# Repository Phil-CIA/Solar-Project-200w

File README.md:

# Solar Project 200W

Solar Project 200W is a prototype-first hardware and firmware effort for a 200W-class solar charging system built around a 4S LiFePO4 battery domain.

## What this repository is for

- Designing and validating a safe MPPT charger path
- Defining control, telemetry, and protection behavior
- Tracking design decisions, handoffs, and bring-up evidence

## Rev2 preparation

Phil selected **retain LM51772 for Rev2**. Open `hardware\kicad\solar-project\Solar Project Rev2.kicad_pro` for new Rev2 work; its schematic/PCB are a metadata-only copy of the reconciled Rev1 development source at `32243b5` (tag `rev2-development-baseline-2026-11-09`), not an implemented or qualified redesign and not for fabrication. See the [revision index](hardware/kicad/solar-project/REVISION-INDEX.md), [consolidation/change register](docs/rev-two-consolidation.md), and current [handoff](HANDOFF.md) for source identity, bench evidence and unresolved work. The controller-comparison requirement in [#20](https://github.com/Phil-CIA/Solar-Project-200w/issues/20) remains open; no BQ25756 evaluation or purchase is requested.

## Rev 1 manufactured baseline

- Only Rev 0 and Rev 1 have been manufactured; Rev 2 is a copied development starting set. Rev 1 is the current production revision. The production release at `C:\Users\user\OneDrive\JLCPCB files\Solar Charger\Rev 1` is authoritative for board identity, manufacturing and board-specific tests. Repository copies support continued development; the schematic, project and BOM differences are described in the board notes.
- Rev 1 is assembled; the supplied manufacturing package and both-side photos are recorded in [board notes](docs/rev-one-board-notes.md).
- Retain the Rev 1 [development tracker](https://github.com/Phil-CIA/Solar-Project-200w/issues/1) and [working plan](docs/rev-one-closure-plan-2026-09-16.md#6-assembled-board-execution-and-issue-1-closure) as qualification references. Later bench findings and current next steps are linked from the handoff; old unpowered checkpoints are not the current board state.
- This is a hobby prototype: keep useful notes and relevant checks, not a formal lab dossier. Assembly does not establish working charging or full-power performance.
- Rev 1 STM32G473 bring-up firmware through `ff89791` is already on `main`; see [firmware notes](firmware/README.md). That is development progress, not proof of board compatibility or a passing powered test.

## System baseline

- PV class: 2x100W panels in parallel (DEC-051)
- Battery class: 12.8V LiFePO4 (4S)
- Rev 1 design targets: 125 W continuous output, 150 W maximum PV operating power, 8-10 A nominal charging, approximately 12 A hardware protection pending verification

## Project structure

- [docs/](docs/): requirements, architecture, decisions, test plans, phase reviews
- [hardware/](hardware/): KiCad files, MPPT notes, wiring maps, implementation checklists
- [firmware/](firmware/): firmware workspace and bring-up software notes

## Start here

1. [HANDOFF.md](HANDOFF.md) - current checkpoint and next step
2. [docs/rev-one-board-notes.md](docs/rev-one-board-notes.md) - working board baseline and known differences
3. [docs/README.md](docs/README.md) - engineering references
4. [docs/decisions-log.md](docs/decisions-log.md) - retained design decisions
5. [SOLAR_HANDOFF_2026-09-19.md](SOLAR_HANDOFF_2026-09-19.md) and [SOLAR_HANDOFF_2026-09-18.md](SOLAR_HANDOFF_2026-09-18.md) for the historical Rev 1 fabrication closeout
6. [hardware/kicad/solar-project/REVISION-INDEX.md](hardware/kicad/solar-project/REVISION-INDEX.md) for KiCad source-of-truth rules

## Simulation workflow

The PV switch gate-drive concept should be verified with SPICE as part of the normal review loop. The project-local LTspice assets are in [hardware/kicad/solar-project/spice](hardware/kicad/solar-project/spice), including the schematic draft [hardware/kicad/solar-project/spice/pv_switch_gate_drive.asc](hardware/kicad/solar-project/spice/pv_switch_gate_drive.asc) and the launcher [hardware/kicad/solar-project/spice/run_ltspice_pv_gate_drive.cmd](hardware/kicad/solar-project/spice/run_ltspice_pv_gate_drive.cmd).

A provisional LTspice integration harness is also present at [hardware/kicad/solar-project/spice/90_system_integration_harness_ltspice.cir](hardware/kicad/solar-project/spice/90_system_integration_harness_ltspice.cir). It is a simplified, staged model of the PV input, buck power stage, and battery boundary. The current run converged to about 13.64 V at the output node and 13.98 V at the battery bus at 4 ms, which is consistent with a basic charging path but still not hardware-validated.

Earlier simulation identified a gate-drive margin problem in the arrangement it modeled. That historical result is not a measured failure of the assembled Rev 1 U14/Q5/Q6 protection circuit; confirm the topology against the Rev 1 production release and use matching low-energy checks before drawing that conclusion.

## Safety notice

This project includes high-current DC power electronics and planned AC-domain integration.
Use staged, current-limited bring-up and treat all safety checks as mandatory gates.

## Session continuity

- [HANDOFF.md](HANDOFF.md)
- [NEXT_CHAT_PROMPT.md](NEXT_CHAT_PROMPT.md)

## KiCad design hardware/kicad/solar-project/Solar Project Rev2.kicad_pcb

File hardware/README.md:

# Hardware

Store hardware development assets here.

Suggested structure:
- `schematics/`
- `pcb/`
- `bom/`
- `manufacturing/`
- `validation/`

Add tool/version notes and board revision history as the project evolves.

## Phase 1 Kickoff Artifacts

- `mppt/block-diagram.md`
- `mppt/schematic-exploration-checklist.md`
- `mppt/interface-assumptions.md`
- `mppt/schematic-notes.md`
- `mppt/net-plan.md`
- `mppt/component-shortlist-template.md`
- `mppt/kicad-implementation-checklist.md`
- `mppt/envelope-decision-worksheet.md`
- `mppt/decision-update-template.md`
- `mppt/buck-topology-notes.md`
- `mppt/github-reference-notes.md`
- `mppt/buck-symbol-placement-checklist.md`
- `mppt/pv-input-stage.md`
- `mppt/pv-input-wiring-map.md`
- `mppt/buck-power-stage-wiring-map.md`
- `mppt/sheet2-component-picks.md`

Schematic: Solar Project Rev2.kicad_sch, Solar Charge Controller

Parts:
10mm1, 10mm2: 10mm LOGO
C1, C8, C12, C22, C28, C33, C44, C45, C46, C47, C48, C51, C54, C57, C58, C59, C60, C64: 100nF; C_0805; Voltage Rated 100V; Tolerance ±10%; Part CL21B104KCFNNNE; LCSC C28233
C2, C55, C56: 1uF; C_0805; Voltage Rated 50V; Tolerance ±10%; Part CL21B105KBFNNNE; LCSC C28323
C3: 100uF; CP_Radial_D6.3mm_P2.50mm; LCSC C49232871
C7: 2.2uF; C_1206; Voltage Rated 100V; Tolerance ±10%; Part CC1206KKX7R0BB225; LCSC C577211
C9, C13: 2.2nF; C_0805; Voltage Rated 50V; Tolerance ±5%; Part CL21C222JBFNNNE; LCSC C28260
C10: 47pF; C_0805; Voltage Rated 50V; Tolerance ±5%; Part CL21C470JBANNNC; LCSC C14857
C14, C53: 100uF; C_1206; Voltage Rated 6.3V; Tolerance ±20%; Part CL31A107MQHNNNE; JLCPCB ID C45783
C15, C34, C35: 2.2uF; C_1206; Voltage Rated 50V; Tolerance ±10%; Part CL31B225KBHNNNE; LCSC C50254
C18: 560uF; CP_Elec_10x12.6; LCSC C264031
C19, C21, C30, C31: 47uF; CP_Radial_D8.0mm_P3.50mm; LCSC C44606514
C20: 180pF; C_0805; LCSC C1794
C23: 100nF; C_0805; LCSC C28233
C24: 22nF; C_0805; LCSC C1710
C25: 1.5nF; C_0805; LCSC C1590
C26: 33nF; C_0805; LCSC C1738
C27, C29: 22uF; C_0805; Voltage Rated 25V; Tolerance ±20%; Part CL21A226MAQNNNE; LCSC C45783
C49, C50: 33pF; C_0805; Voltage Rated 50V; Tolerance ±5%; Part CC0805JRNPO9BN330; LCSC C1798
C52: 220nF; C_0805; Voltage Rated 50V; Tolerance ±10%; Part CL21B224KBFNNNE; LCSC C5378
C61: DNP; C_0805; Voltage Rated 100V; Tolerance ±10%; Part CL21B104KCFNNNE; not fitted
C62, C63: 100nF; C_0805_2012Metric; Voltage Rated 100V; Tolerance ±10%; Part CL21B104KCFNNNE; LCSC C28233
D1, D5: 1SMA4742A; D_DO-214AC(SMA); Part 1SMA4742A; LCSC C19077480
D2: SMBJ48CA; D_SMB; Part SMBJ48CA; LCSC C151264
D3: USBLC6-2SC6; SOT-23-6; MPN USBLC6-2SC6; Digi-Key_PN 497-5235-1-ND
D6, D7, D10: 1N5819WS; D_SOD-323; Forward Voltage (Vf@If) 600mV@1A; Reverse Voltage (Vr) 40V; Part 1N5819WS; LCSC C191023
D8, D11: WS2812B; LED-SMD_4P-L1.6-W1.5_XL-1615RGBC-WS2812B; LCSC C5349954
D9: Green; D_0805; Forward Voltage (VF) 1.6V~2.6V; Part KT-0805G; LCSC C2297
D12: Yellow; D_0805; Forward Voltage (VF) 1.6V~2.6V; Part KT-0805Y; LCSC C2296
F1, F2: 3522-2; Automotive fuse holder keystone 3522-2_KEY; Part - USA Keystone 3522-2, sourced via Digikey/Mo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; LCSC C3204137
J1, J3: Screw_Terminal_01x02; TerminalBlock_Phoenix_MKDS-1,5-2-5.08_1x02_P5.08mm_Horizont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; LCSC C8439
J2: USB4105-GF-A; GCT_USB4105-GF-A; PARTREV B4; LCSC C3020560
J7: Fan; PinHeader_1x03_P2.54mm_Vertical; LCSC C29275
J8: I2C bus; PinHeader_1x04_P2.54mm_Vertical
J9: FTSH-105-01-L-DV-007-K; MPN FTSH-105-01-L-DV-007-K; LCSC C5160761
JP1: SolderJumper_2_Bridged; SolderJumper-2_P1.3mm_Bridged_Pad1.0x1.5mm
JP2: SolderJumper_2_Open; SolderJumper-2_P1.3mm_Open_RoundedPad1.0x1.5mm
L2: L; L_APV_APH1240; LCSC C49308530
L3: L; L_KOHERelec_MDA7030; LCSC C49333024
M1, M2, M3, M4: CSD18540Q5B; TDSON-8-1; LCSC C86513
NT1, NT2, NT3, NT4, NT5, NT6, NT7, NT8: NetTie_2; NetTie-2_SMD_Pad0.5mm
Q2, Q3, Q7: 2N7002K; Q_SOT-23; Part 2N7002K; LCSC C22379475
Q4: HSBA0119; PQFN-8-EP_6x5mm_P1.27mm_Generic; LCSC C53244070
Q5, Q6: BSC040N10NS5; TDSON-8-1; LCSC C534334
R1, R2, R32, R38, R67: 100kΩ; R_0805; Overload Voltage (Max) 150V; Tolerance ±1%; Part 0805W8F1003T5E; LCSC C17416
R3: 76.8k; R_0805; LCSC C3000581; not fitted
R4, R26, R27, R41, R65, R69, R70, R71, R72, R73: 10Ω; R_0805; Overload Voltage (Max) 150V; Tolerance ±1%; Part 0805W8F100JT5E; LCSC C17414
R5, R44, R45: 4.7kΩ; R_0805; Overload Voltage (Max) 150V; Tolerance ±1%; Part 0805W8F4701T5E; LCSC C17673
R6, R19, R34, R36, R47, R48, R52, R53, R54, R55, R56, R57, R58, R59, R82, R86, R91, R92, R93, R94, R95, R96, R97, R98, R100: 10kΩ; R_0805; Overload Voltage (Max) 150V; Tolerance ±1%; Part 0805W8F1002T5E; LCSC C17414
R7, R10, R61: 20kΩ; R_0805; Overload Voltage (Max) 150V; Tolerance ±1%; Part 0805W8F2002T5E; LCSC C17523
R8: 27kΩ; R_0805; Overload Voltage (Max) 150V; Tolerance ±1%; Part 0805W8F2702T5E; LCSC C17547
R9: 180k; R_0805; LCSC C17497
R11, R39: 330Ω; R_0805; Overload Voltage (Max) 150V; Tolerance ±1%; Part 0805W8F3300T5E; LCSC C17650
R12: 6.8kΩ; R_0805; Overload Voltage (Max) 150V; Tolerance ±1%; Part 0805W8F6801T5E; LCSC C17730
R13: 1MΩ; R_0805; Overload Voltage (Max) 150V; Tolerance ±1%; Part 0805W8F1004T5E; LCSC C17514
R14: 330kΩ; R_0805; Overload Voltage (Max) 150V; Tolerance ±1%; Part 0805W8F3303T5E; LCSC C17651
R15: 2kΩ; R_0805; Overload Voltage (Max) 150V; Tolerance ±1%; Part 0805W8F2001T5E; LCSC C17537
R16, R22, R75, R80: 5mΩ; RES_2012_SUS- wide 0805; Tolerance ±1%; Part KRL2012E-M-R005-F-T5; LCSC C2073455
R17: 5.62k; R_0805; LCSC C2933470
R18: 76.8k; R_0805; LCSC C3000581
R20: 499k; R_0805; LCSC C119857
R21: 102k; R_0805; LCSC C119830
R23: 75kΩ; R_0805; Overload Voltage (Max) 150V; Tolerance ±1%; Part 0805W8F7502T5E; LCSC C17743
R24, R62: 5.1kΩ; R_0805; Overload Voltage (Max) 150V; Tolerance ±1%; Part 0805W8F5101T5E; LCSC C17700
R25: 5.62k; R_0805; LCSC C2933470; not fitted
R28: 51.7k; R_0805; LCSC C119851
R29: 20.5k; R_0805; LCSC C119842
R30: 40.2k; R_0805; LCSC C119848
R31: 2.43k; R_0805; LCSC C119853
R33, R49, R63, R64: 0Ω; R_0805; Overload Voltage (Max) 150V; Tolerance ±1%; Part 0805W8F0000T5E; LCSC C17888
R35, R81: 180kΩ; R_0805; Overload Voltage (Max) 150V; Tolerance ±1%; Part 0805W8F1803T5E; LCSC C17497
R37, R66: 2.2MΩ; R_0805; Overload Voltage (Max) 150V; Tolerance ±1%; Part 0805W8F2204T5E; LCSC C17539
R40, R43, R74: 100kΩ; R_0805; Overload Voltage (Max) 150V; Tolerance ±1%; Part Number RC0603FR-07100KL; JLCPCB ID C25803
R42, R83, R84, R85: 1kΩ; R_0805; Overload Voltage (Max) 150V; Tolerance ±1%; Part 0805W8F1001T5E; LCSC C17513
R46: 32.4kΩ; R_0805; Overload Voltage (Max) 150V; Tolerance ±1%; Part RC0805FR-0732K4L; LCSC C2930193
R50: 10kΩ; R_0805; Overload Voltage (Max) 150V; Tolerance ±1%; Part 0805W8F1002T5E; LCSC C17415; not fitted
R51: 12kΩ; R_0805; Overload Voltage (Max) 150V; Tolerance ±1%; Part 0805W8F1202T5E; LCSC C17444
R60: 1.5kΩ; R_0805; Overload Voltage (Max) 150V; Tolerance ±1%; Part 0805W8F1501T5E; LCSC C17515
R68: 1.3k; R_0805; LCSC C2933303
R76, R77: KRL2012E-M-R005-F-T5; RES_2012_SUS- wide 0805; Tolerance ±1%; Part KRL2012E-C-R010-F-T5; LCSC C2073455
R78, R79: .001; R_2512_6332Metric; Tolerance ±1%; Part DSLR-M-3-1F; LCSC C41382682
R87, R88, R89, R90: 100Ω; R_0805; Overload Voltage (Max) 150V; Tolerance ±1%; Part 0805W8F1000T5E; LCSC C17408
R99: 56kΩ; R_0805; Overload Voltage (Max) 150V; Tolerance ±1%; Part 0805W8F5602T5E; LCSC C17756
R101: 33kΩ; R_0805; Overload Voltage (Max) 150V; Tolerance ±1%; Part 0805W8F3302T5E; LCSC C17633
S1: Tactile Button, 160gf; SW_TS-1088-AR02016; Voltage Rating (Dc) 12V; Part TS-1088-AR02016; LCSC C720477
SW1, SW2, SW3, SW4, SW5: Tactile Button, 160gf; SW-SMD_4P-L5.1-W5.1-P3.70-LS6.5-TL-2; Voltage Rating (Dc) 12V; Part TS-1187A-B-A-B; LCSC C318884
TP1: TestPoint_Small; PinHeader_1x01_P2.54mm_Vertical; not fitted
TP15, TP16, TP17, TP18: 5015; TestPoint_Keystone_5015_Micro_Mini; PARTREV F; LCSC C5199798
U1: STM32G473CEU6; QFN-48-1EP_7x7mm_P0.5mm_EP5.6x5.6mm; LCSC C1342773
U2: ESP32-C3 SuperMini (16-pin); ESP32 C3 mini
U3: CP2102-GMR; WQFN-28_L5.0-W5.0-P0.50-BL-EP3.2; Supply Voltage 3V~3.6V; Part CP2102-GMR; LCSC C6568
U4: LM5163; Texas_R-PDSO-G8_EP2.95x4.9mm_Mask2.4x3.1mm_ThermalVias; LCSC C2873264
U5: LP5912-3.3DRV; WSON-6-1EP_2x2mm_P0.65mm_EP1x1.6mm_ThermalVias; LCSC C114569
U6: LM51772QRHARQ1; VFQFN-40-1EP_6x6mm; LCSC C41383743
U7: AHT20; Humidity sensor; PARTREV V1.0; LCSC C2757850
U8: SSD1306_OLED; 0.96 inOLED display SSD1306; LCSC C5248080
U9: LMV393; SOIC-8-1EP_3.9x4.9mm_P1.27mm_EP2.29x3mm_ThermalVias; LCSC C7984
U10, U11, U12: INA241A3IDDFR; TSOT-23-8; Part INA241A3IDDFR; LCSC C129346
U14: LM74502HDDFR; Texas_DDF0008A_SOT-8_1.6x2.9mm_P0.65mm; LCSC C5219202
U15: TXU0204PWR; TSSOP-14_4.4x5mm_P0.65mm; LCSC C4363888
X2: X49SM8MSD2SC; CRYSTAL-SMD_L11.5-W4.8-LS12.7; Frequency Tolerance ±20ppm; Part X49SM8MSD2SC; LCSC C12674

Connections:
BATT_PACK_POS: J3.2, NT8.1, R78.1, R79.1, R99.1
BTN_DN_N: SW2.1 (A), U1.33 (PA11)
BTN_ENT_N: SW5.1 (A), U1.47 (PB9)
BTN_LT_N: SW4.1 (A), U1.34 (PA12)
BTN_RT_N: SW3.1 (A), U1.39 (PC10)
BTN_UP_N: SW1.1 (A), U1.38 (PA15)
CHG_OUT_POS: D6.2, F2.3, F2.4, J7.3, Q6.5 (D), R20.1, R81.1, U6.18 (VOUT)
CTRL_3V3: C12.1, C44.1, C48.1, C53.1, C54.1, C55.1, C63.1, J8.3, J9.1 (VTref), R5.2, R19.1, R21.1, R34.1, R39.1, R44.1, R45.1, R51.1, R53.1, R54.1, R55.1, R56.1, R57.1, R58.1, R59.1, R74.1, R91.1, R92.1, R97.1, R98.1, TP17.1, U1.1 (VBAT), U1.20 (VREF+), U1.21 (VDDA), U1.23 (VDD), U1.35 (VDD), U1.48 (VDD), U3.6 (VDD), U5.1 (OUT), U6.38 (RST), U7.2 (VDD), U8.2 (VCC), U9.8 (V+), U11.7 (REF1), U15.1 (VCCA), U15.8 (OE)
CTRL_5V: C9.1, C14.1, C51.2, C56.1, C57.1, D7.1, D8.2 (VDD), D10.1, D11.2 (VDD), L3.2, R10.2, R11.1, TP18.1, U2.16 (5V), U5.4 (EN), U5.6 (IN), U10.6 (V+), U11.6 (V+), U12.6 (V+)
CTRL_EN_CHG: R73.1, U1.25 (PB12)
CTRL_SUPPLY_IN: C15.1, D6.1, R13.1, U4.2 (VIN)
CTS: U1.14 (PA6), U3.23 (CTS)
ESP_3V3_U2: C62.1, R93.1, R94.1, R95.1, R96.1, U2.14 (3.3V), U15.14 (VCCB)
ESP_CONSOLE_RX: R88.2, R96.2, U2.7 (GPIO20)
ESP_CONSOLE_RX_STM: R92.2, U1.22 (PB10), U15.3 (A2)
ESP_CONSOLE_TX: R94.2, U2.8 (GPIO21), U15.10 (B4)
ESP_CONSOLE_TX_STM: R90.1, R98.2, U1.24 (PB11)
ESP_DATA_RX: R87.2, R95.2, U2.9 (GPIO0)
ESP_DATA_RX_STM: R91.2, U1.41 (PB3), U15.2 (A1)
ESP_DATA_TX: R93.2, U2.10 (GPIO1), U15.11 (B3)
ESP_DATA_TX_STM: R89.1, R97.2, U1.42 (PB4)
FAN_TACH: J7.2, U1.43 (PB5)
FAULT_OCP: R53.2, U1.17 (PB0), U9.7
FAULT_OVP: R19.2, U1.18 (PB1), U9.1
Fan Control: R4.1, U1.40 (PC11)
HO1: M1.4 (G), R69.1
HO2: M4.4 (G), R71.1
I2C CLK: J8.1, R44.2, U1.45 (PB7), U6.6 (SCL_CFG4), U7.3 (SCL), U8.3 (SLC)
I2C DATA: J8.4, R45.2, U1.44 (PB6), U6.5 (SDA_CFG3), U7.4 (SDA), U8.4 (SDA)
I_BATT_+: NT7.1, U11.8 (+)
I_BATT_-: NT8.2, U11.1 (-)
I_in_+: NT4.1, U12.8 (+)
I_in_-: NT3.1, U12.1 (-)
LO1: M2.4 (G), R70.1
LO2: M3.4 (G), R72.1
unnamed: C9.2, C10.1, R12.2
unnamed: C24.1, R31.1
unnamed: D8.4 (DIN), U1.19 (PB2)
unnamed: D9.2, R11.2
unnamed: D8.1 (DOUT), D11.4 (DIN)
unnamed: D12.2, R39.2
unnamed: F2.1, F2.2, NT7.2, R78.2, R79.2
unnamed: F1.3, F1.4, J1.1
unnamed: J2.A5 (CC1), R24.2
unnamed: J2.B5 (CC2), R62.2
unnamed: D3.3 (I/O2), J2.A7 (DN1), J2.B7 (DN2)
unnamed: D3.1 (I/O1), J2.A6 (DP1), J2.B6 (DP2)
unnamed: J2.A8 (SBU1), J2.B8 (SBU2)
unnamed: J7.1, Q3.3 (D)
unnamed: JP1.1 (A), JP2.1 (A), U6.14 (FB_INT)
unnamed: Q2.3 (D), R42.1, R43.2
unnamed: Q2.1 (G), R40.2, R41.2
unnamed: Q3.1 (G), R1.1, R4.2
unnamed: D1.2, Q4.4 (G), R42.2
unnamed: D5.1, Q5.4 (G), Q6.4 (G), R2.2, R65.2
unnamed: Q7.1 (G), R73.2, R74.2
unnamed: R7.2, R10.1
unnamed: R9.1, R12.1
unnamed: R14.2, R15.1
unnamed: R37.2, R66.1
unnamed: R46.1, R68.1
unnamed: R60.1, R61.2
unnamed: R84.1, U12.5
unnamed: R85.1, U11.5
unnamed: R99.2, R100.1, R101.1
unnamed: R54.2, SW1.2 (B)
unnamed: R55.2, SW2.2 (B)
unnamed: R56.2, SW3.2 (B)
unnamed: R57.2, SW4.2 (B)
unnamed: R58.2, SW5.2 (B)
unnamed: R86.1, U1.46 (PB8-BOOT0)
unnamed: C50.1, U1.5 (PF0-OSC_IN), X2.1
unnamed: C49.1, U1.6 (PF1-OSC_OUT), X2.2
unnamed: D3.6 (I/O1), U3.4 (D+)
unnamed: D3.4 (I/O2), U3.5 (D-)
unnamed: R5.1, U3.9 (RST#)
unnamed: C13.2, U4.7 (BST)
unnamed: R13.2, R14.1, U4.3 (EN/UVLO)
unnamed: C10.2, R6.2, R7.1, U4.5 (FB)
unnamed: R8.1, U4.4 (RON)
unnamed: C13.1, L3.1, R9.2, U4.8 (SW)
unnamed: R33.1, U6.9 (ADDR_SLOPE_CFG1)
unnamed: R30.1, U6.10 (CDC)
unnamed: R29.1, U6.8 (CFG2)
unnamed: C24.2, C25.2, U6.13 (COMP)
unnamed: C20.1, C61.1, R26.2, U6.22 (CSA)
unnamed: C20.2, C61.2, R27.2, U6.21 (CSB)
unnamed: C22.1, U6.25 (HB1)
unnamed: C23.1, U6.31 (HB2)
unnamed: R69.2, U6.24 (HO1)
unnamed: R71.2, U6.32 (HO2)
unnamed: R68.2, U6.16 (ILIMCOMP_ISET)
unnamed: R63.1, U6.19 (ISNSN)
unnamed: R64.1, U6.20 (ISNSP)
unnamed: R70.2, U6.27 (LO1)
unnamed: R72.2, U6.30 (LO2)
unnamed: R32.2, U6.7 (MODE)
unnamed: R28.1, U6.12 (RT)
unnamed: C26.2, U6.2 (SS_ATRK)
unnamed: C27.1, C46.1, U6.1 (VCC1)
unnamed: U7.1 (NC), U7.6 (NC)
unnamed: R65.1, U14.6 (GATE)
unnamed: R66.2, R67.1, U14.7 (OV)
unnamed: C52.2, U14.4 (VCAP)
unnamed: R89.2, U15.4 (A3Y)
unnamed: R90.2, U15.5 (A4Y)
unnamed: R87.1, U15.13 (B1Y)
unnamed: R88.1, U15.12 (B2Y)
OCP_MEAS: R49.1, R83.1, U10.5
OCP_REF: R51.2, R52.1, U9.6 (-)
OCP_SENSE: R49.2, R50.1, U9.5 (+)
OVP_REF: R21.2, R48.1, U9.2 (-)
OVP_SENSE: R20.2, R47.1, U9.3 (+)
PA0: C58.1, R83.2, U1.8 (PA0)
PA1: C59.1, R84.2, U1.9 (PA1)
PC4: C60.1, R85.2, U1.16 (PC4)
PV_FUSED_POS: D2.2, F1.1, F1.2, NT4.2, R35.1, R76.1, R77.1
PV_IN_POS: C7.1, C8.1, C19.1, C21.1, C28.1, C30.1, C31.1, M1.5 (D), Q4.5 (D), R18.1, R23.1, TP16.1, U6.36 (VIN), U6.40 (BIAS)
PV_Q4_SOURCE: D1.1, NT3.2, Q4.1 (S), Q4.2 (S), Q4.3 (S), R43.1, R76.2, R77.2
PWR_NEG: C1.2, C2.2, C3.2, C7.2, C8.2, C12.2, C14.2, C15.2, C18.2, C19.2, C21.2, C25.1, C26.1, C27.2, C28.2, C29.2, C30.2, C31.2, C33.1, C34.2, C35.2, C44.2, C45.2, C46.2, C47.2, C48.2, C49.2, C50.2, C51.1, C53.2, C54.2, C55.2, C56.2, C57.2, C58.2, C59.2, C60.2, C62.2, C63.2, C64.2, D2.1, D3.2 (GND), D8.3 (GND), D9.1, D11.3 (GND), D12.1, J1.2, J2.A1_B12 (GND), J2.B1_A12 (GND__1), J2.SH1 (SHELL_GND), J2.SH2 (SHELL_GND__1), J2.SH3 (SHELL_GND__2), J2.SH4 (SHELL_GND__3), J3.1, J8.2, J9.3 (GND), J9.5 (GND), J9.9 (GNDDetect), M2.1 (S), M2.2 (S), M2.3 (S), M3.1 (S), M3.2 (S), M3.3 (S), Q2.2 (S), Q3.2 (S), Q7.2 (S), R1.2, R6.1, R8.2, R15.2, R17.2, R24.1, R25.2, R28.2, R29.2, R30.2, R31.2, R33.2, R36.2, R38.2, R40.1, R46.2, R47.2, R48.2, R50.2, R52.2, R60.2, R62.1, R67.2, R82.2, R86.2, R100.2, S1.2 (B), SW1.3 (C), SW1.4 (D), SW2.3 (C), SW2.4 (D), SW3.3 (C), SW3.4 (D), SW4.3 (C), SW4.4 (D), SW5.3 (C), SW5.4 (D), TP15.1, U1.49 (VSS), U2.15 (GND), U3.3 (GND), U4.1 (GND), U4.9 (TH_pd), U5.5 (GND), U5.7 (EP), U6.3 (SYNC), U6.4 (DTRK), U6.17 (AGND), U6.28 (PGND), U6.41 (GND), U7.5 (GND), U8.1 (GND), U8.5 (GND), U8.6 (GND), U8.7 (GND), U8.8 (GND), U9.4 (V-), U9.9 (EP), U10.2 (GND), U10.3 (REF2), U10.4 (GND), U10.7 (REF1), U11.2 (GND), U11.3 (REF2), U11.4 (GND), U12.2 (GND), U12.3 (REF2), U12.4 (GND), U12.7 (REF1), U14.2 (GND), U15.7 (GND)
RTS: U1.15 (PA7), U3.24 (RTS)
RXD: U1.31 (PA9), U3.25 (RXD)
SRC: D5.2, Q5.1 (S), Q5.2 (S), Q5.3 (S), Q6.1 (S), Q6.2 (S), Q6.3 (S), R2.1, U14.8 (SRC)
STM_NRST: C47.1, J9.10 (~RESET), R59.2, S1.1 (A), U1.7 (PG10-~RST)
SWCLK: J9.4 (SWCLK/TCK), U1.37 (PA14)
SWDIO: J9.2 (SWDIO/TMS), U1.36 (PA13)
SW_1: C22.2, M1.1 (S), M1.2 (S), M1.3 (S), M2.5 (D), NT2.2, R22.1, R75.1, U6.23 (SW1)
SW_1_+: NT2.1, R26.1
SW_1_-: L2.1, NT1.1, NT1.2, R22.2, R27.1, R75.2
SW_2: C23.2, L2.2, M3.5 (D), M4.1 (S), M4.2 (S), M4.3 (S), U6.33 (SW2)
TXD: U1.32 (PA10), U3.26 (TXD)
U6_FLT: R34.2, U1.2 (PC13), U6.11 (FLT)
U6_VCC2: C29.1, C45.1, JP1.2 (B), R32.1, U6.29 (VCC2)
VBUS: C1.1, C2.1, D3.5 (VBUS), D7.2, D10.2, J2.A4_B9 (VBUS), J2.B4_A9 (VBUS__1), U3.7 (REGIN), U3.8 (VBUS)
V_BATT_ADC: C64.1, R101.2, U1.11 (PA3)
V_in_ADC: R35.2, R36.1, U1.12 (PA4)
V_in_FB: R17.1, R18.2, U6.15 (VIN-FB)
V_in_ON: R41.1, U1.13 (PA5)
V_out: C3.1, C18.1, C33.2, C34.1, C35.1, M4.5 (D), NT5.2, R3.1, R16.1, R80.1
V_out _on: R38.1, U1.30 (PA8), U14.1 (EN_UVLO)
V_out_ADC: R81.2, R82.1, U1.10 (PA2)
V_out_SNS_N: NT6.1, R63.2, U10.1 (-)
V_out_SNS_P: NT5.1, R64.2, U10.8 (+)
V_out_sense: C52.1, NT6.2, Q5.5 (D), R16.2, R37.1, R80.2, TP1.1 (1_1), U14.5 (VS)
_OUTPUT Feedback: JP2.2 (B), R3.2, R25.1
_Undervoltage Feedback: Q7.3 (D), R23.2, R61.1, U6.37 (EN_UVLO)

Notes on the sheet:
Batt temp Sensor
Nav Buttons
zone A
5 Volt Buck
OLED Display
Output Protection
Zone C
DEbugging conn
WiFi
Fan Control
Temp and Humidity sensor Board

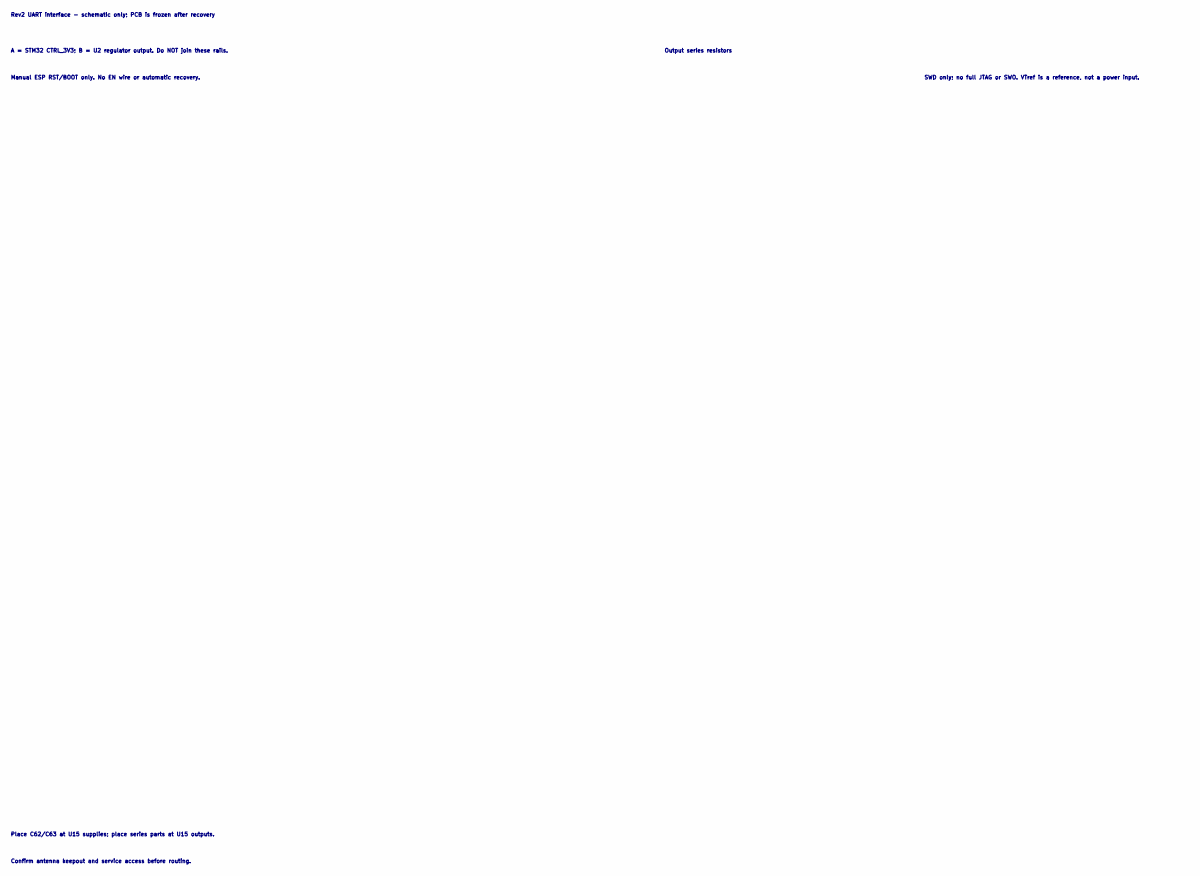
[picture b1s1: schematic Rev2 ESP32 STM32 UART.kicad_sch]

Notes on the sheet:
Confirm antenna keepout and service access before routing.
Place C62/C63 at U15 supplies; place series parts at U15 outputs.
Rev2 UART interface - schematic only; PCB is frozen after recovery
Manual ESP RST/BOOT only. No EN wire or automatic recovery.
A = STM32 CTRL_3V3; B = U2 regulator output. Do NOT join these rails.
SWD only; no full JTAG or SWO. VTref is a reference, not a power input.
Output series resistors

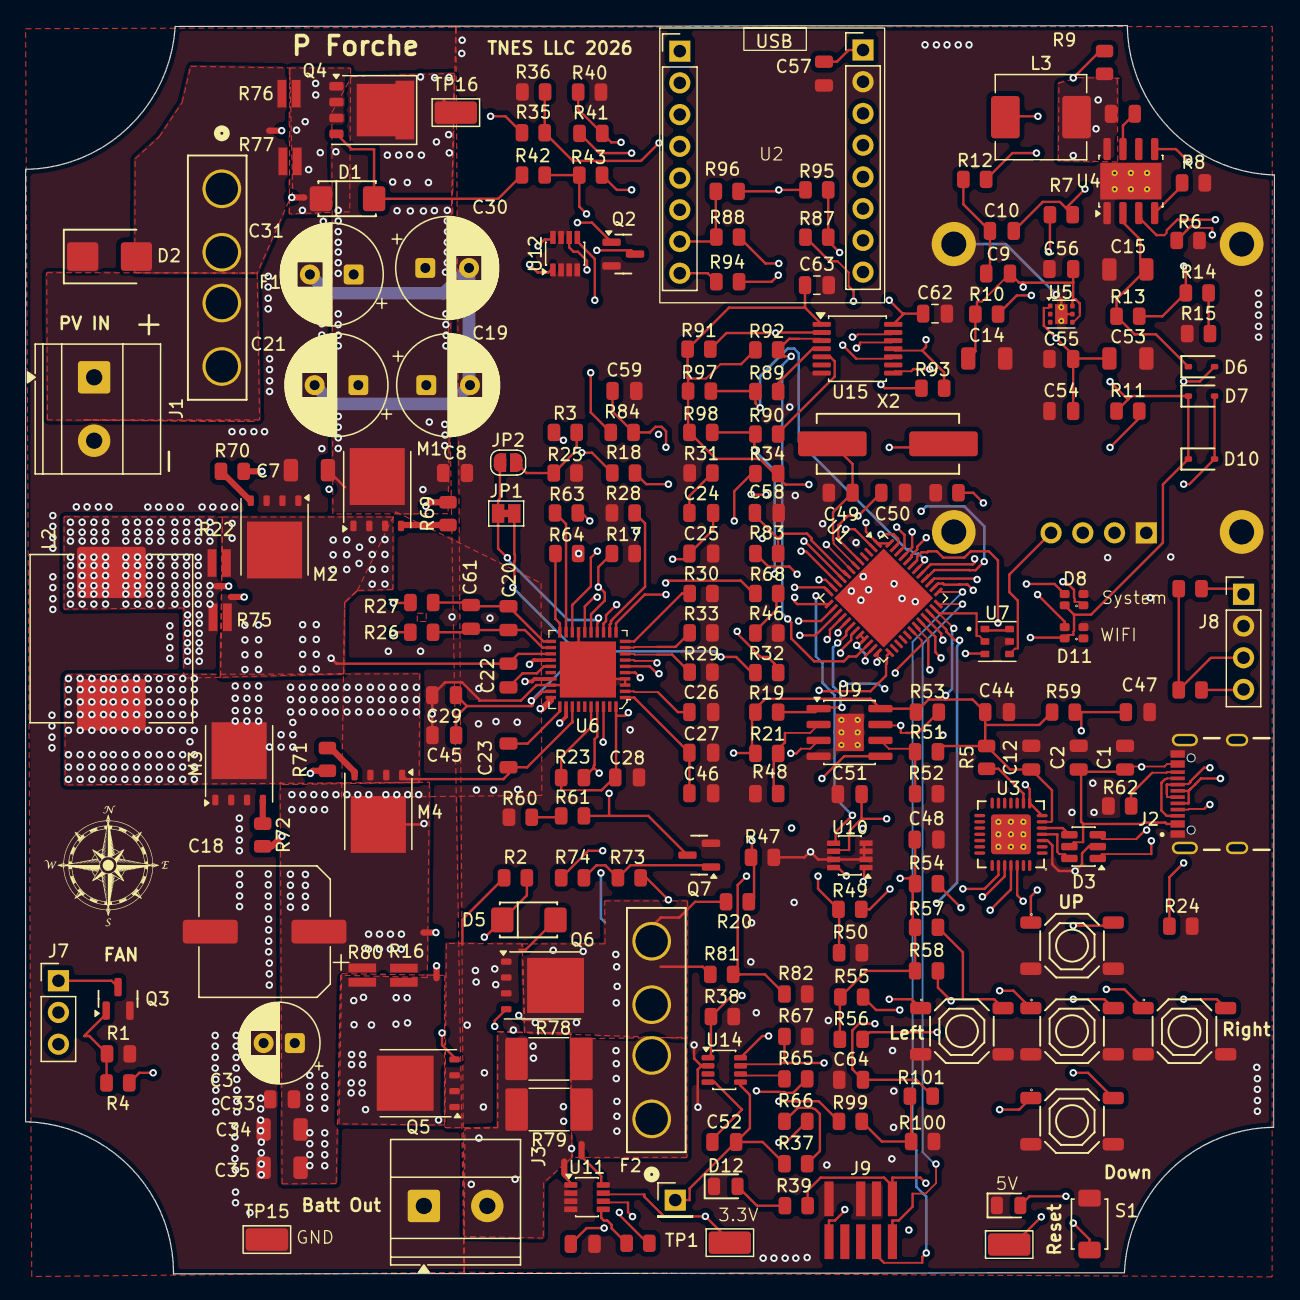
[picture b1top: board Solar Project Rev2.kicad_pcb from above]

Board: 4 copper layers, 100.0 x 99.9 mm, 219 parts (1 on the bottom side), 146 nets.

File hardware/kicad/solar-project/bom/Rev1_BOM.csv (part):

Item #,Designator,Qty,Value,Footprint,LCSC Part #,Description
1,"10mm1, 10mm2",2,,1My_Parts_ Passive:10mm LOGO,,
2,"C1, C8, C12, C22, C28, C33, C44, C45, C46, C47, C48, C51, C52, C54, C57",15,100nF,PCM_JLCPCB:C_0805,C28233,100V 100nF X7R ±10% 0805 Multilayer Ceramic Capacitors MLCC - SMD/SMT ROHS
3,"C2, C55, C56",3,1uF,PCM_JLCPCB:C_0805,C28323,50V 1uF X7R ±10% 0805 Multilayer Ceramic Capacitors MLCC - SMD/SMT ROHS
4,C3,1,100uF,Capacitor_THT:CP_Radial_D6.3mm_P2.50mm,C49232871,Unpolarized capacitor
5,"C7, C15, C34, C35",4,2.2uF,PCM_JLCPCB:C_1206,C50254,50V 2.2uF X7R ±10% 1206 Multilayer Ceramic Capacitors MLCC - SMD/SMT ROHS
6,"C9, C13",2,2.2nF,PCM_JLCPCB:C_0805,C28260,50V 2.2nF C0G ±5% 0805 Multilayer Ceramic Capacitors MLCC - SMD/SMT ROHS
7,C10,1,47pF,PCM_JLCPCB:C_0805,C14857,50V 47pF C0G ±5% 0805 Multilayer Ceramic Capacitors MLCC - SMD/SMT ROHS
8,"C14, C53",2,100uF,PCM_JLCPCB:C_1206,C15008,6.3V 100uF X5R ±20% 1206 Multilayer Ceramic Capacitors MLCC - SMD/SMT ROHS
9,C18,1,560uF,Capacitor_SMD:CP_Elec_10x12.6,C264031,Unpolarized capacitor
10,"C19, C21, C30",3,47uF,Capacitor_THT:C_Radial_D8.0mm_H7.0mm_P3.50mm,C44606514,Unpolarized capacitor
11,C20,1,180pF,PCM_JLCPCB:C_0805,C1794,Unpolarized capacitor
12,C23,1,100nF,PCM_JLCPCB:C_0805,C28233,Unpolarized capacitor
13,C24,1,22nF,PCM_JLCPCB:C_0805,C1710,Unpolarized capacitor
14,C25,1,1.5nF,PCM_JLCPCB:C_0805,C1590,Unpolarized capacitor
15,C26,1,33nF,PCM_JLCPCB:C_0805,C1738,Unpolarized capacitor
16,"C27, C29",2,22uF,PCM_JLCPCB:C_0805,C45783,25V 22uF X5R ±20% 0805 Multilayer Ceramic Capacitors MLCC - SMD/SMT ROHS
17,C31,1,47uF,Capacitor_THT:CP_Radial_D8.0mm_P3.50mm,C44606514,Unpolarized capacitor
18,"C49, C50",2,33pF,PCM_JLCPCB:C_0805,C1798,50V 33pF NP0 ±5% 0805 Multilayer Ceramic Capacitors MLCC - SMD/SMT ROHS
19,"D1, D5",2,1SMA4742A,PCM_JLCPCB:D_DO-214AC(SMA),C19077480,Independent Type 11.4V~12.6V 1W 12V SMA(DO-214AC) Zener Diodes ROHS
20,D2,1,SMBJ60CA,PCM_JLCPCB:D_SMB,C19077593,6.2A 600W 96.8V 73.7V Bidirectional 60V SMB ESD and Surge Protection (TVS/ESD) ROHS
21,D3,1,USBLC6-2SC6,Package_TO_SOT_SMD:SOT-23-6,C7519,"Very low capacitance ESD protection diode, 2 data-line, SOT-23-6"
22,"D4, D6, D7, D10",4,1N5819WS,PCM_JLCPCB:D_SOD-323,C191023,40V 600mV@1A 1A SOD-323 Schottky Diodes ROHS
23,D8,1,WS2812B,PCM_JLCPCB:LED-SMD_4P-L1.6-W1.5_XL-1615RGBC-WS2812B,C5349954,1615 RGB LEDs(Built-in IC) ROHS
24,D9,1,Green,PCM_JLCPCB:D_0805,C2297,Emerald 0805 LED Indication - Discrete ROHS
25,D12,1,Yellow,PCM_JLCPCB:D_0805,C2296,Yellow 0805 LED Indication - Discrete ROHS
26,"F1, F2",2,Fuse,Fuse:Fuseholder_Littelfuse_100_series_5x25mm,C142864,Fuse
27,"J1, J3",2,Screw_Terminal_01x02,"TerminalBlock_Phoenix:TerminalBlock_Phoenix_MKDS-1,5-2-5.08_1x02_P5.08mm_Horizontal",C8439,"Generic screw terminal, single row, 01x02, script generated (kicad-library-utils/schlib/autogen/connector/)"
28,J2,1,USB4105-GF-A,1My_Parts_ Connectors:GCT_USB4105-GF-A,C3020560,
29,J4,1,Conn_01x04,Connector_PinHeader_2.54mm:PinHeader_1x04_P2.54mm_Vertical_SMD_Pin1Right,C41417361,"Generic connector, single row, 01x04, script generated (kicad-library-utils/schlib/autogen/connector/)"
30,J5,1,Conn_01x03_Socket,Connector_PinHeader_2.54mm:PinHeader_1x03_P2.54mm_Vertical,C2937625,"Generic connector, single row, 01x03, script generated"
31,J6,1,20021121-00010C4LF,digikey-footprints:PinHeader_2x5_P1.27mm,,
32,L2,1,L,Inductor_SMD:L_APV_APH1240,C49308530,Inductor
33,L3,1,L,Inductor_SMD:L_KOHERelec_MDA7030,C49333024,Inductor
34,"M1, M2, M3, M4",4,CSD18540Q5B,Package_TO_SOT_SMD:TDSON-8-1,C86513,"100A Id, 60V Vds, NexFET N-Channel Power MOSFET, 2.2mOhm Ron, 41nC Qg(typ), SON8 5x6mm"
35,"Q2, Q3, Q7",3,2N7002K,PCM_JLCPCB:Q_SOT-23,C22379475,"60V 340mA 350mW 900mΩ@10V,500mA 2.5V@1mA 1PCSNChannel SOT-23 MOSFETs ROHS"
36,Q4,1,HSBA0119,Package_DFN_QFN:PQFN-8-EP_6x5mm_P1.27mm_Generic,C53244070,P-MOSFET transistor
37,"Q5, Q6",2,BSC040N10NS5,Package_TO_SOT_SMD:TDSON-8-1,C534334,"100A Id, 100V Vds, OptiMOS N-Channel Power MOSFET, 4.0mOhm Ron, Qg (typ) 58.0nC, PG-TDSON-8"
38,"R1, R2, R32, R38, R40, R43, R67, R74",8,100kΩ,PCM_JLCPCB:R_0805,C17416,125mW Thick Film Resistors 150V ±100ppm/°C ±1% 100kΩ 0805 Chip Resistor - Surface Mount ROHS
39,R3,1,76.8k,PCM_JLCPCB:R_0805,C3000581,ResistorRES 76.8kΩ ±1% 125mW 0805
40,"R4, R26, R27, R41, R65, R69, R70, R71, R72, R73",10,10Ω,PCM_JLCPCB:R_0805,C17414,125mW Thick Film Resistors 150V ±1% ±200ppm/°C 10Ω 0805 Chip Resistor - Surface Mount ROHS
41,"R5, R44, R45",3,4.7kΩ,PCM_JLCPCB:R_0805,C17673,125mW Thick Film Resistors 150V ±100ppm/°C ±1% 4.7kΩ 0805 Chip Resistor - Surface Mount ROHS
42,"R6, R19, R34, R36, R47, R48, R50, R53, R54, R55, R56, R57, R58, R59",14,10kΩ,PCM_JLCPCB:R_0805,C17415,125mW Thick Film Resistors 150V ±100ppm/°C ±1% 10kΩ 0805 Chip Resistor - Surface Mount ROHS
43,"R7, R10, R61",3,20kΩ,PCM_JLCPCB:R_0805,C17523,125mW Thick Film Resistors 150V ±100ppm/°C ±1% 20kΩ 0805 Chip Resistor - Surface Mount ROHS
44,R8,1,27kΩ,PCM_JLCPCB:R_0805,C17547,125mW Thick Film Resistors 150V ±100ppm/°C ±1% 27kΩ 0805 Chip Resistor - Surface Mount ROHS
45,R9,1,180k,PCM_JLCPCB:R_0805,C17497,Resistor
46,"R11, R39",2,330Ω,PCM_JLCPCB:R_0805,C17650,125mW Thick Film Resistors 150V ±100ppm/°C ±1% 330Ω 0805 Chip Resistor - Surface Mount ROHS
47,R12,1,6.8kΩ,PCM_JLCPCB:R_0805,C17730,125mW Thick Film Resistors 150V ±100ppm/°C ±1% 6.8kΩ 0805 Chip Resistor - Surface Mount ROHS
48,R13,1,1MΩ,PCM_JLCPCB:R_0805,C17514,125mW Thick Film Resistors 150V ±100ppm/°C ±1% 1MΩ 0805 Chip Resistor - Surface Mount ROHS
49,R14,1,330kΩ,PCM_JLCPCB:R_0805,C17651,125mW Thick Film Resistors 150V ±100ppm/°C ±1% 330kΩ 0805 Chip Resistor - Surface Mount ROHS
50,R15,1,2kΩ,PCM_JLCPCB:R_0805,C17537,125mW Thick Film Resistors 150V ±100ppm/°C ±1% 2kΩ 0805 Chip Resistor - Surface Mount ROHS
51,"R16, R22",2,0.001ohms,Resistor_SMD:R_Shunt_Vishay_WSK2512_6332Metric_T2.66mm,C41382682,Shunt resistor with Kelvin connections
52,R17,1,5.62k,PCM_JLCPCB:R_0805,C2933470,Resistor RES 5.62kΩ ±1% 125mW 0805
53,R18,1,76.8k,PCM_JLCPCB:R_0805,C3000581,Resistor RES 76.8kΩ ±1% 125mW 0805
54,R20,1,499k,PCM_JLCPCB:R_0805,C119857,Resistor
55,R21,1,102k,PCM_JLCPCB:R_0805,C119830,Resistor
56,R23,1,75kΩ,PCM_JLCPCB:R_0805,C17743,125mW Thick Film Resistors 150V ±100ppm/°C ±1% 75kΩ 0805 Chip Resistor - Surface Mount ROHS
57,"R24, R62",2,5.1kΩ,PCM_JLCPCB:R_0805,C17700,125mW Thick Film Resistors 150V ±100ppm/°C ±1% 5.1kΩ 0805 Chip Resistor - Surface Mount ROHS
58,R25,1,5.62k,PCM_JLCPCB:R_0805,C2933470,Resistor  RES 5.62kΩ ±1% 125mW 0805
59,R28,1,51.7k,PCM_JLCPCB:R_0805,C119851,Resistor
60,R29,1,20.5k,PCM_JLCPCB:R_0805,C119842,Resistor
61,R30,1,40.2k,PCM_JLCPCB:R_0805,C119848,Resistor
62,R31,1,2.43k,PCM_JLCPCB:R_0805,C119853,Resistor
63,"R33, R49, R63, R64",4,0Ω,PCM_JLCPCB:R_0805,C17888,125mW Thick Film Resistors 150V ±800ppm/°C ±1% 0Ω 0805 Chip Resistor - Surface Mount ROHS
64,R35,1,180kΩ,PCM_JLCPCB:R_0805,C17497,125mW Thick Film Resistors 150V ±100ppm/°C ±1% 180kΩ 0805 Chip Resistor - Surface Mount ROHS
65,"R37, R66",2,2.2MΩ,PCM_JLCPCB:R_0805,C17539,125mW Thick Film Resistors 150V ±100ppm/°C ±1% 2.2MΩ 0805 Chip Resistor - Surface Mount ROHS
66,"R42, R52",2,1kΩ,PCM_JLCPCB:R_0805,C17513,125mW Thick Film Resistors 150V ±100ppm/°C ±1% 1kΩ 0805 Chip Resistor - Surface Mount ROHS
67,R46,1,82kΩ,PCM_JLCPCB:R_0805,C17840,125mW Thick Film Resistors 150V ±100ppm/°C ±1% 82kΩ 0805 Chip Resistor - Surface Mount ROHS
68,R51,1,2.7kΩ,PCM_JLCPCB:R_0805,C17546,125mW Thick Film Resistors 150V ±100ppm/°C ±1% 2.7kΩ 0805 Chip Resistor - Surface Mount ROHS
69,R60,1,1.5kΩ,PCM_JLCPCB:R_0805,C17515,125mW Thick Film Resistors 150V ±100ppm/°C ±1% 1.5kΩ 0805 Chip Resistor - Surface Mount ROHS
70,R68,1,1.3k,PCM_JLCPCB:R_0805,C2933303,Resistor
71,S1,1,"Tactile Button, 160gf",PCM_JLCPCB:SW_TS-1088-AR02016,C720477,Without 50mA 4mm 100MΩ 100000 Times 12V 160gf 3mm 2mm Round Button Standing paste SPST SMD Tactile Switches ROHS
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
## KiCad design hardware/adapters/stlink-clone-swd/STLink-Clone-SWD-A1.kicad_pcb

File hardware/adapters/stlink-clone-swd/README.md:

# ST-Link clone to Cortex SWD adapter - A1

Original **32 x 24 mm, two-layer prototype** for the clone pinout in Phil's
product photo. This is a separate accessory; it does not change controller
J9 or any solar-controller CAD.

The previously researched `noahp/stlink-clone-adapter` project was reference
research only. Its CAD, routing, artwork and third-party assets are not copied
into this design or the order package. This design uses the observed signal
mapping, original schematic/PCB geometry, and published connector dimensions.

**Prototype fabrication files, not a bench-qualified accessory.** Confirm the
actual clone pinout, connector orientation and housing fit before connection.
No PCB or components have been ordered by this tooling.

## Saved prototype status - 2026-11-20

The user reports ordering the adapter PCB. The supplier, uploaded file,
quantity and order confirmation have not been independently recorded.
Physical fit, cable continuity and bench operation remain unverified;
issue #17 stays open.

The committed PCB preserves the user's subsequent KiCad edits: rotated and
relocated J1/J2, rerouted copper, a rounded outline approximately
31.93 x 23.85 mm, four vias, and an optional local J1 STEP-model reference.
The STEP model itself is not included or needed for fabrication.

KiCad 10.0.6 checks on this saved layout report **zero ERC findings, zero
unconnected items and zero schematic/PCB parity findings**, but **three DRC
track-width violations**: three SWCLK segments are 0.15 mm wide against the
configured 0.20 mm minimum. Independent copper checks confirm the intended
signal mapping, isolated probe power outputs/VTref and open reset link.
The width violations remain outstanding; this snapshot is not DRC-clean.

The earlier generated fabrication ZIP and attached order package describe
the original rectangular layout, not this edited layout. The earlier Gerber
ZIP SHA-256 is
`b8cfb77ba3782303a6683d0b4219555f69d448b7bfb49cd07f1b22f03e529070`.
Do not assume it is the file actually submitted to the supplier.
Retain the actual uploaded ZIP with the order confirmation.

**Do not run `generate.py` over the saved layout to export it.** That script
recreates the original rectangular design, overwriting the user's CAD edits.
Use it only in a separate copy when reproducing the original baseline.
Before another fabrication release, resolve the width violations and export
fresh Gerbers/drills from the reviewed saved PCB in KiCad.

## What to order

Run `generate.py` with KiCad 10's bundled Python to create the `build` folder.
The settings below describe that original generated baseline, not the edited
snapshot above. For example, from a separate copy of this directory in PowerShell:

```powershell
& 'C:\Users\user\AppData\Local\Programs\KiCad\10.0\bin\python.exe' '.\generate.py'
```

Upload **`build\STLink-Clone-SWD-A1-gerbers.zip`**, not the entire source or
order-package archive, to the PCB manufacturer's Gerber uploader.

| Fabrication setting | Prototype selection |
|---|---|
| Board type | Bare PCB; assemble connectors by hand |
| Quantity | Suggested first order: 5 |
| Dimensions | 32 x 24 mm, one rectangular board |
| Layers | 2 |
| Material / thickness | FR-4, 1.6 mm |
| Copper | 1 oz |
| Finish | Lead-free HASL; ENIG is also suitable |
| Mask / legend | Both sides; green mask / white legend is fine |
| Smallest track / clearance | 0.25 mm / 0.20 mm design minimum |
| Smallest finished hole | 0.30 mm plated via |
| Connector holes | Ten 1.02 mm finished plated holes |
| Special processing | None; no impedance control, castellations or slots |
| Stencil / assembly | Not required for the proposed hand-assembled order |

Review the manufacturer's rendered layers before paying: check two copper
layers, mask openings, legible pin-1 markers, a single 32 x 24 mm outline and
12 plated holes. There are ten connector holes and two vias, with no NPTH
holes. Do not select an SMT assembly service without supplying and reviewing
its separate assembly requirements.

### Purchased parts, per assembled adapter

| Item | Qty | Part / requirement |
|---|---:|---|
| J1 | 1 | Samtec **SSW-105-02-G-D**, female 2x5 2.54 mm through-hole socket |
| J2 | 1 | Samtec **FTSH-105-01-L-DV-007-K**, keyed 2x5 1.27 mm SMT male header, pin 7 omitted |
| JP1 | 0 | PCB solder-link pads only; leave open |
| Cable | 1 | Samtec **FFSD-05-D-04.00-01-N** candidate: dual-ended 1.27 mm ribbon, nominal 4 inches |

The cable's official product page lists FTSH as a mating family, and the FTSH
print specifies `-K` for FFSD mating. This is manufacturer-document evidence,
not a physical cable check. Use the normal wiring version, not `-RW`/reversed
variants; check pin-1-to-pin-1 continuity and key alignment before use.

J2 intentionally uses the same candidate as the controller's standard J9, so
the ribbon has female sockets at both ends. J1 is a **female socket**, not
another male pin header. Fit it on the top/component side. Its socket pin 1
is the square PCB pad marked `1`; align that cavity with the clone's actual
pin 1. Its mating-face view is mirrored relative to its PCB solder view.
Do not force a socket into an incompatible clone shroud. Check shroud opening,
male post dimensions, insertion depth, and clearance to the adapter board.
An unkeyed J1 can be reversed; its pin-1 marker must be followed.

The SSW tail drawing specifies approximately 0.79 x 0.41 mm flat tails;
1.02 mm finished holes and 1.70 mm annular pads are the selected prototype
land pattern. J1 uses 2.54 mm position and row pitch, a 13.21 x 4.95 mm
nominal body, and a 4.93 mm tail. Trim soldered tails if needed for clearance.
J2 uses the official 1.27 mm pitch / 3.43 mm row-spacing SMT land pattern
with 0.74 x 2.79 mm lands, a 6.35 x 6.86 mm outline, and pad 7 omitted.

## Electrical mapping

This is the **type-B/Variant-2** clone mapping shown on the supplied photo.
It is not a universal adapter for every stick marked ST-LINK/V2.

| Clone J1 | Signal | Cortex J2 / controller J9 |
|---:|---|---|
| 1 | Clone RST | Pin 10 only if JP1 is bridged |
| 2 | SWCLK | 4 |
| 3 | SWIM | Isolated |
| 4 | SWDIO | 2 |
| 5, 6 | Ground | 3, 5, 9 |
| 7, 8 | Probe 3.3 V outputs | Isolated |
| 9, 10 | Probe 5 V outputs | Isolated |
| None | Target VTref | J2.1 is isolated |
| None | SWO / TDI | J2.6 / J2.8 are isolated |
| None | Key | J2 pin 7 physically omitted |

**Power the controller normally.** There is no probe-to-target power path.
This adapter is specifically for the fixed-level clone in the photo, which
shows no VTref input. It is not a universal replacement for an adapter used
with voltage-sensing professional probes. Do not use it to program targets
with incompatible logic voltage.

**Leave JP1 open initially.** Some clones expose an STM8/SWIM reset signal
rather than STM32 NRST. Only bridge JP1 after verifying the actual probe's
STM32 reset support. With JP1 open, use normal SWD attach, not an expectation
of connect-under-reset recovery. The target's own reset circuit remains intact.

## Assembly and first-use checks

1. Inspect bare boards and verify that the power pads listed as isolated do
   not have continuity to ground or any target-side contact. Verify JP1 is open.
2. Solder J1 and J2 on the marked component side, following each pin-1 marker.
   Do not populate pin 7 on J2 or bridge JP1 during routine assembly.
3. Before plugging into the target, verify J1.2 to J2.4, J1.4 to J2.2, and
   J1.5/6 to J2.3/5/9. Verify J1.1 does not reach J2.10 with JP1 open.
4. With the actual probe unpowered, confirm its pinout rather than trusting
   casing text alone; some clone batches are mislabeled. Ground-pair
   continuity alone is a useful check, not full pinout verification.
5. Verify the cable numbering/keying and physical fit, then attach to a
   normally powered 3.3 V target and try a conservative SWD clock such as
   100 kHz. Bench attach/programming remains to be demonstrated.

Do not treat the solar controller as bench-ready simply because this adapter
passes CAD checks. Its separate board-completion and powered-test gates remain.

## Original generated baseline validation

The generator runs KiCad 10 netlist export, ERC, zone-refilled DRC and
schematic parity with violation exit codes enabled. It separately verifies
the exact schematic pin groups and actual copper connectivity, including
isolation of every probe power output, VTref and the open reset link.

The original rectangular A1 outputs were generated with **KiCad 10.0.6**.
These results do not describe the subsequently edited, committed PCB; see
the saved prototype status above.

| Check | Result |
|---|---|
| ERC | 0 findings |
| DRC | 0 findings |
| Unconnected items | 0 |
| Schematic/PCB parity | 0 findings |
| Active copper mapping | Matches the table above |
| Probe power / target VTref / open reset | Copper-isolated as specified |
| Outline / layers / thickness | Closed 32 x 24 mm / 2 / 1.6 mm |
| Drill export | Ten 1.02 mm holes and two 0.30 mm vias |

Reports, a BOM, schematic PDF, top/bottom SVG previews and source/Gerber
hashes are in `build`. The order-package ZIP includes these and editable
source; the smaller Gerber ZIP is the file to upload for bare PCB fabrication.
Do not upload an old ZIP after changing the CAD: export and check fresh files
from the intended layout, without overwriting it with the baseline generator.

No enclosure fit, clone housing fit, actual cable continuity, or bench
attach/program validation has been performed. Order only a small prototype
batch until those physical checks pass.

## Manufacturer references

- [SSW-105-02-G-D product](https://www.samtec.com/products/ssw-105-02-g-d)
- [SSW through-hole print](https://suddendocs.samtec.com/prints/ssw-1xx-xx-xxx-x-xx-xxx-xx-mkt.pdf)
- [FTSH-105-01-L-DV-007-K product](https://www.samtec.com/products/ftsh-105-01-l-dv-007-k)
- [FTSH recommended land pattern](https://suddendocs.samtec.com/prints/ftsh-1xx-xx-xxx-dv-xxx-footprint.pdf)
- [FTSH print and FFSD key option](https://suddendocs.samtec.com/prints/ftsh-1xx-xx-xxx-dv-xxx-xxx-x-xx-mkt.pdf)
- [FFSD-05-D-04.00-01-N cable candidate](https://www.samtec.com/products/ffsd-05-d-04.00-01-n)
- [FFSD cable print / wiring options](https://suddendocs.samtec.com/prints/ffsd-xx-x-xx.xx-01-x-x-xxx-mkt.pdf)

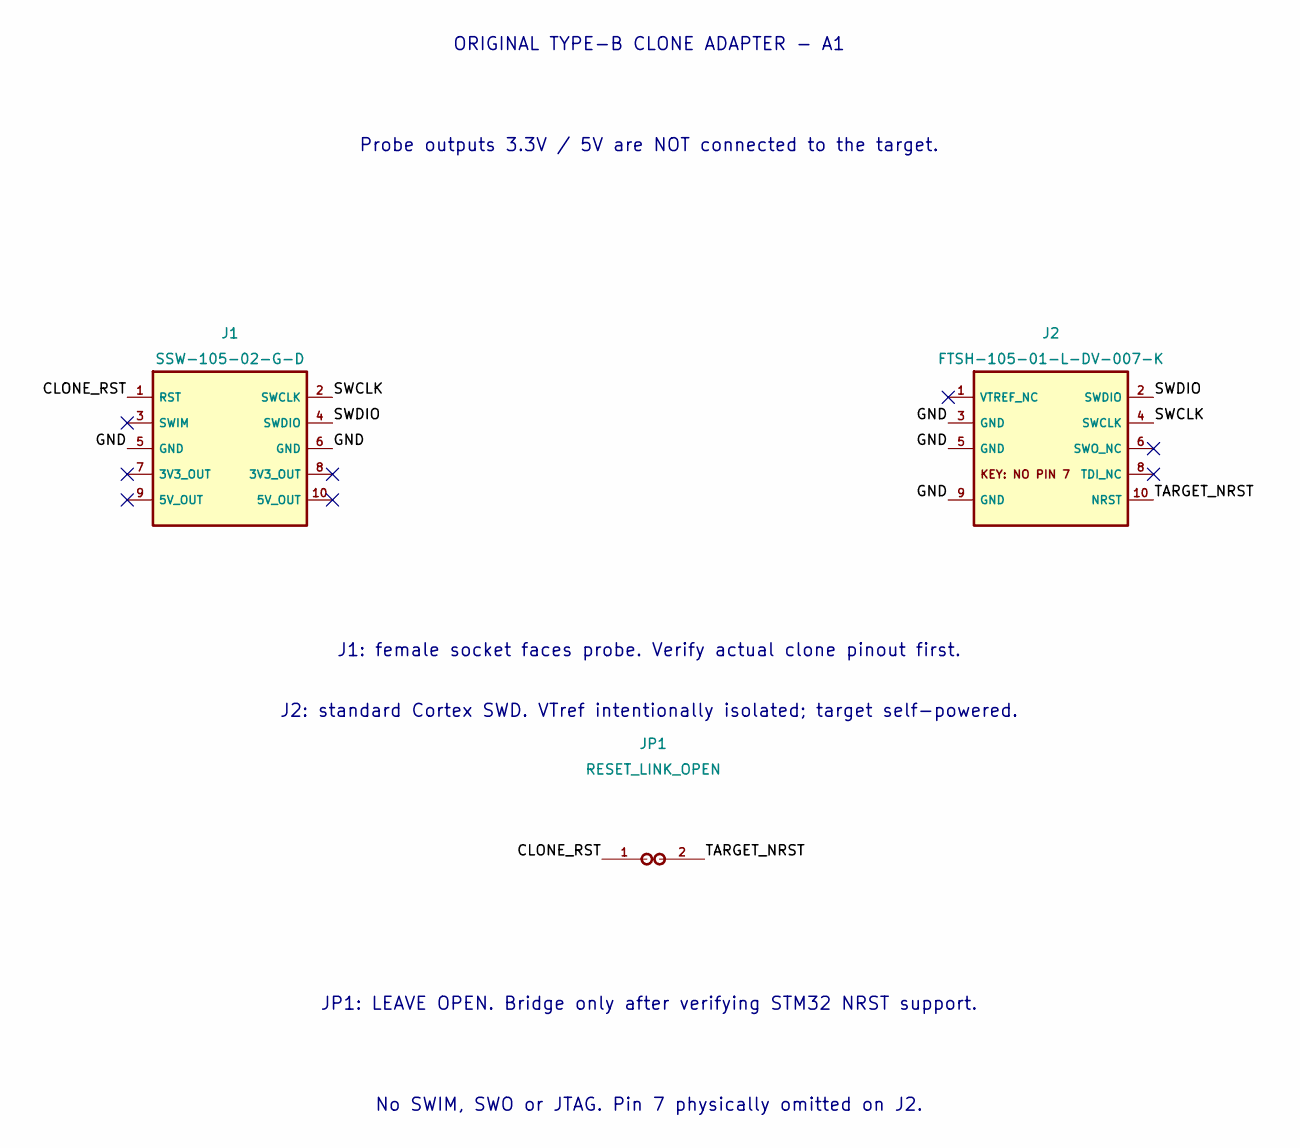
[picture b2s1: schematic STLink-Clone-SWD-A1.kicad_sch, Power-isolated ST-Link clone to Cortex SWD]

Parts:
J1: SSW-105-02-G-D
J2: FTSH-105-01-L-DV-007-K
JP1: RESET_LINK_OPEN; Reset-Link-Open

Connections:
/CLONE_RST: J1.1 (RST), JP1.1
/GND: J1.5 (GND), J1.6 (GND), J2.3 (GND), J2.5 (GND), J2.9 (GND)
/SWCLK: J1.2 (SWCLK), J2.4 (SWCLK)
/SWDIO: J1.4 (SWDIO), J2.2 (SWDIO)
/TARGET_NRST: J2.10 (NRST), JP1.2

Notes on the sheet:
ORIGINAL TYPE-B CLONE ADAPTER - A1
Probe outputs 3.3V / 5V are NOT connected to the target.
J1: female socket faces probe. Verify actual clone pinout first.
J2: standard Cortex SWD. VTref intentionally isolated; target self-powered.
JP1: LEAVE OPEN. Bridge only after verifying STM32 NRST support.
No SWIM, SWO or JTAG. Pin 7 physically omitted on J2.

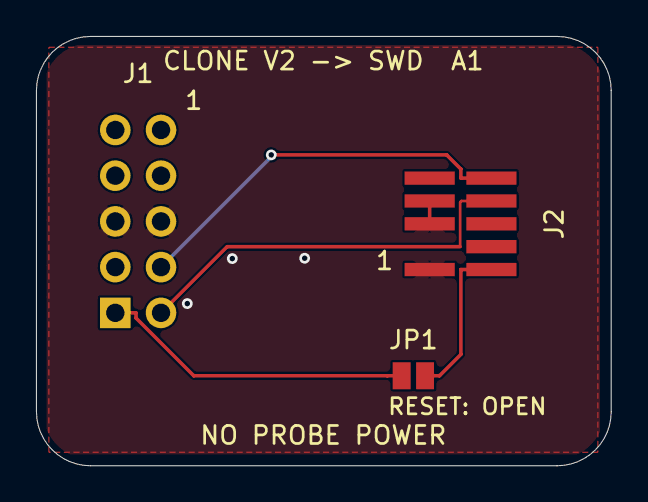
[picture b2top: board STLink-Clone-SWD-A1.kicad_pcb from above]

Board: 2 copper layers, 31.9 x 23.8 mm, 3 parts (0 on the bottom side), 5 nets.
